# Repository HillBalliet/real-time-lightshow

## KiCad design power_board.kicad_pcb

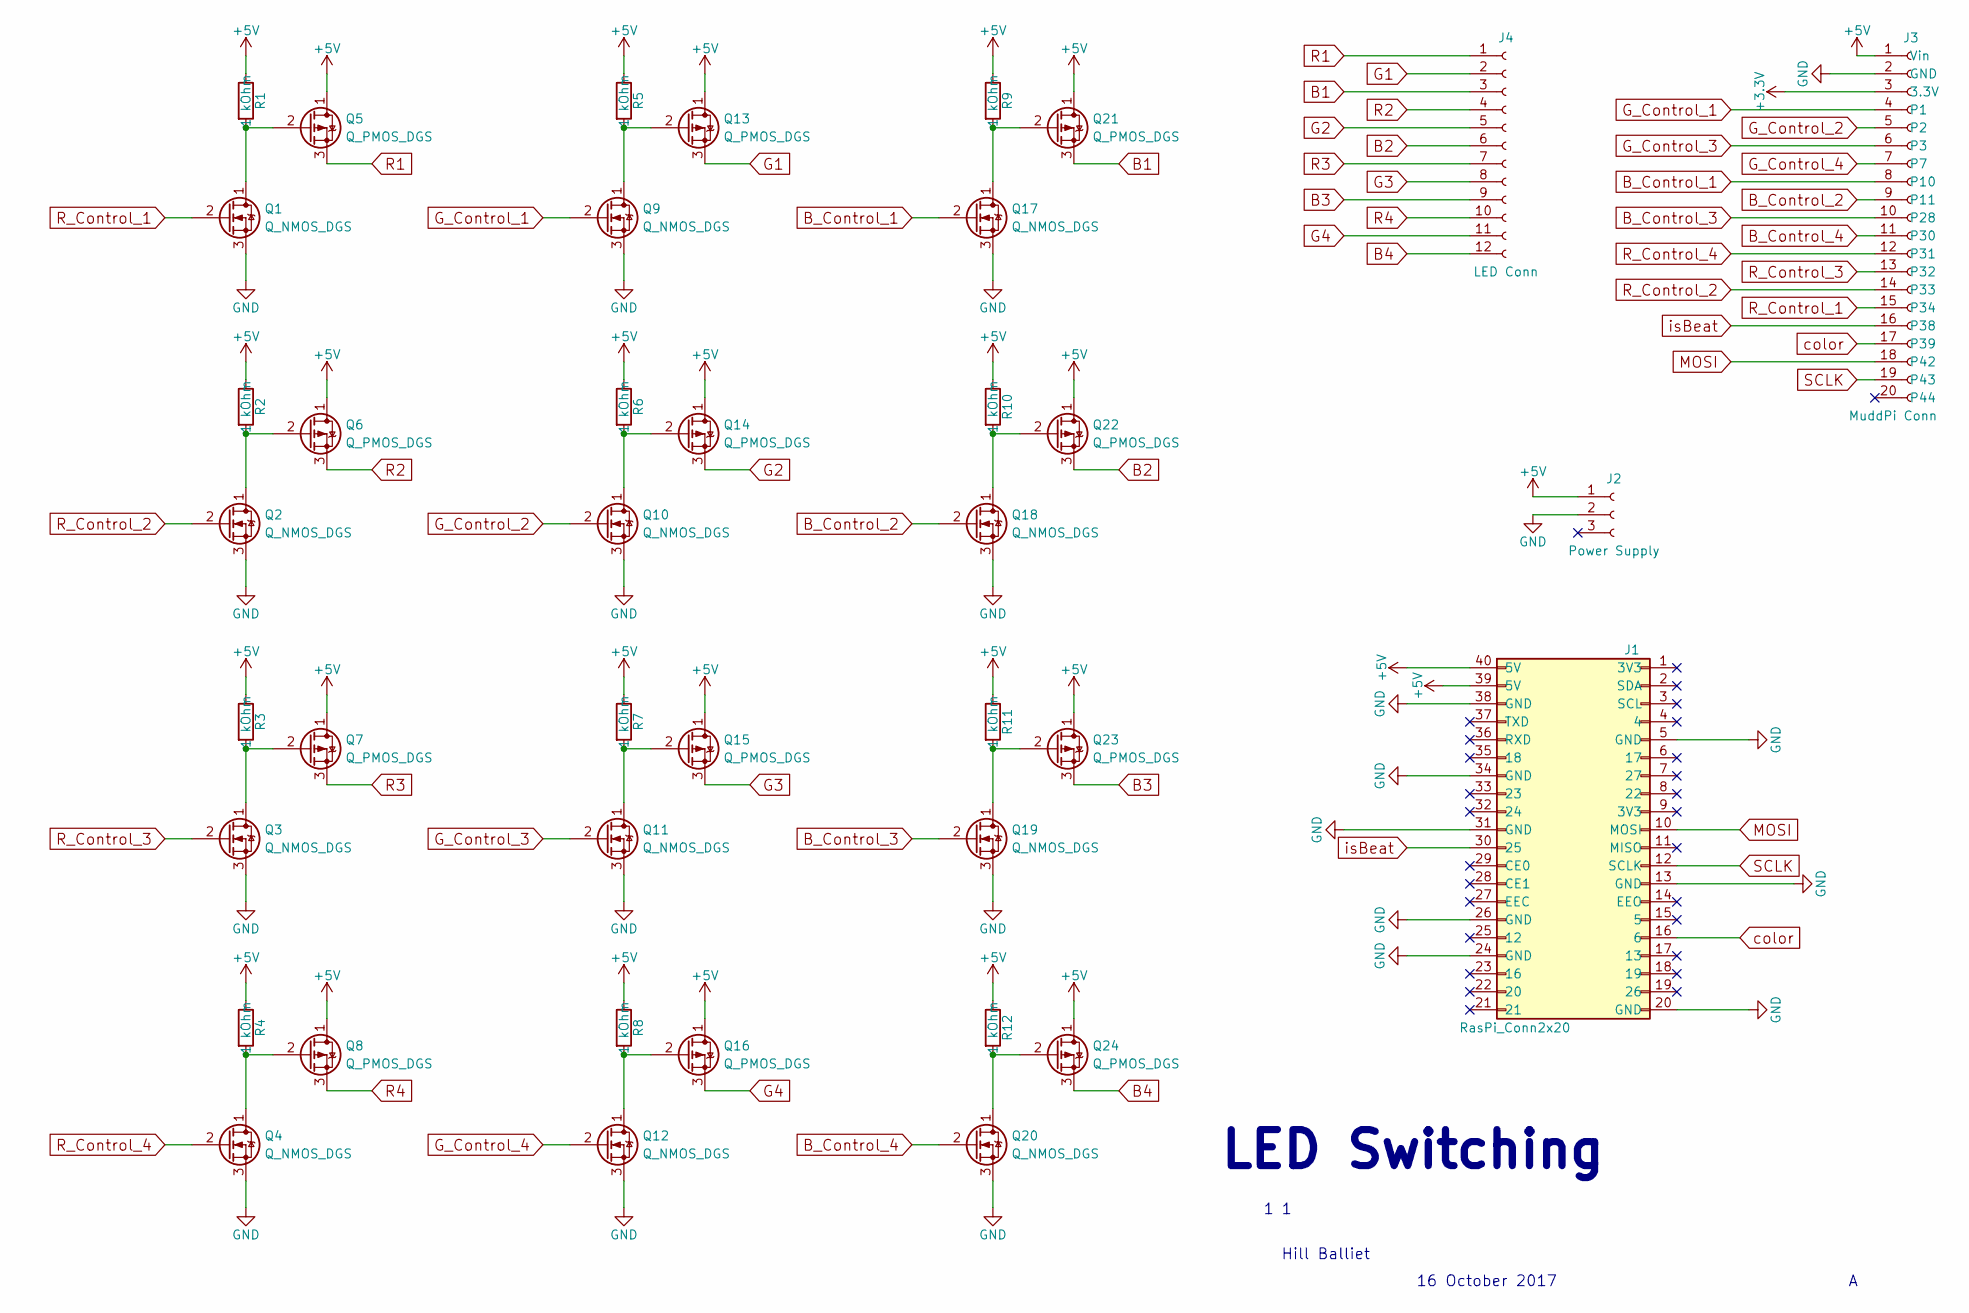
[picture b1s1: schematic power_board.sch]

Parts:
J1: RasPi_Conn2x20; Molex_2x20
J2: Power Supply; BARREL_JACK
J3: MuddPi Conn; Molex_1x20; Manufacturer PN PPPC201LFBN-RC
J4: LED Conn; Molex_KK-6410-12_12x2.54mm_Straight
Q1, Q2, Q3, Q4, Q9, Q10, Q11, Q12, Q17, Q18, Q19, Q20: Q_NMOS_DGS; SOT-323FL; Drive Voltage 0.9, 4.5V; Manufacturer PN RU1J002YNTCL
Q5, Q6, Q7, Q8, Q13, Q14, Q15, Q16, Q21, Q22, Q23, Q24: Q_PMOS_DGS; SOT-23; Drive Voltage 2.5, 4.5V; Manufacturer PN DMP2215L-7
R1, R2, R3, R4, R5, R6, R7, R8, R9, R10, R11, R12: 1 kOhm; R_0402; Manufacturer PN CRG0402J1K0

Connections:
+3V3: J3.3 (3.3V)
+5V: J1.39 (5V), J1.40 (5V), J2.1, J3.1 (Vin), Q5.1 (D), Q6.1 (D), Q7.1 (D), Q8.1 (D), Q13.1 (D), Q14.1 (D), Q15.1 (D), Q16.1 (D), Q21.1 (D), Q22.1 (D), Q23.1 (D), Q24.1 (D), R1.1, R2.1, R3.1, R4.1, R5.1, R6.1, R7.1, R8.1, R9.1, R10.1, R11.1, R12.1
B1: J4.3, Q21.3 (S)
B2: J4.6, Q22.3 (S)
B3: J4.9, Q23.3 (S)
B4: J4.12, Q24.3 (S)
B_Control_1: J3.8 (P10), Q17.2 (G)
B_Control_2: J3.9 (P11), Q18.2 (G)
B_Control_3: J3.10 (P28), Q19.2 (G)
B_Control_4: J3.11 (P30), Q20.2 (G)
G1: J4.2, Q13.3 (S)
G2: J4.5, Q14.3 (S)
G3: J4.8, Q15.3 (S)
G4: J4.11, Q16.3 (S)
GND: J1.5 (GND), J1.13 (GND), J1.20 (GND), J1.24 (GND), J1.26 (GND), J1.31 (GND), J1.34 (GND), J1.38 (GND), J2.2, J3.2 (GND), Q1.3 (S), Q2.3 (S), Q3.3 (S), Q4.3 (S), Q9.3 (S), Q10.3 (S), Q11.3 (S), Q12.3 (S), Q17.3 (S), Q18.3 (S), Q19.3 (S), Q20.3 (S)
G_Control_1: J3.4 (P1), Q9.2 (G)
G_Control_2: J3.5 (P2), Q10.2 (G)
G_Control_3: J3.6 (P3), Q11.2 (G)
G_Control_4: J3.7, Q12.2 (G)
MOSI: J1.10 (MOSI), J3.18 (P42)
unnamed: Q1.1 (D), Q5.2 (G), R1.2
unnamed: Q2.1 (D), Q6.2 (G), R2.2
unnamed: Q3.1 (D), Q7.2 (G), R3.2
unnamed: Q4.1 (D), Q8.2 (G), R4.2
unnamed: Q10.1 (D), Q14.2 (G), R6.2
unnamed: Q11.1 (D), Q15.2 (G), R7.2
unnamed: Q12.1 (D), Q16.2 (G), R8.2
unnamed: Q9.1 (D), Q13.2 (G), R5.2
unnamed: Q17.1 (D), Q21.2 (G), R9.2
unnamed: Q18.1 (D), Q22.2 (G), R10.2
unnamed: Q19.1 (D), Q23.2 (G), R11.2
unnamed: Q20.1 (D), Q24.2 (G), R12.2
R1: J4.1, Q5.3 (S)
R2: J4.4, Q6.3 (S)
R3: J4.7, Q7.3 (S)
R4: J4.10, Q8.3 (S)
R_Control_1: J3.15 (P34), Q1.2 (G)
R_Control_2: J3.14 (P33), Q2.2 (G)
R_Control_3: J3.13 (P32), Q3.2 (G)
R_Control_4: J3.12 (P31), Q4.2 (G)
SCLK: J1.12 (SCLK), J3.19 (P43)
color: J1.16 (6), J3.17 (P39)
isBeat: J1.30 (25), J3.16 (P38)

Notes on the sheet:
LED Switching
16 October 2017
Hill Balliet

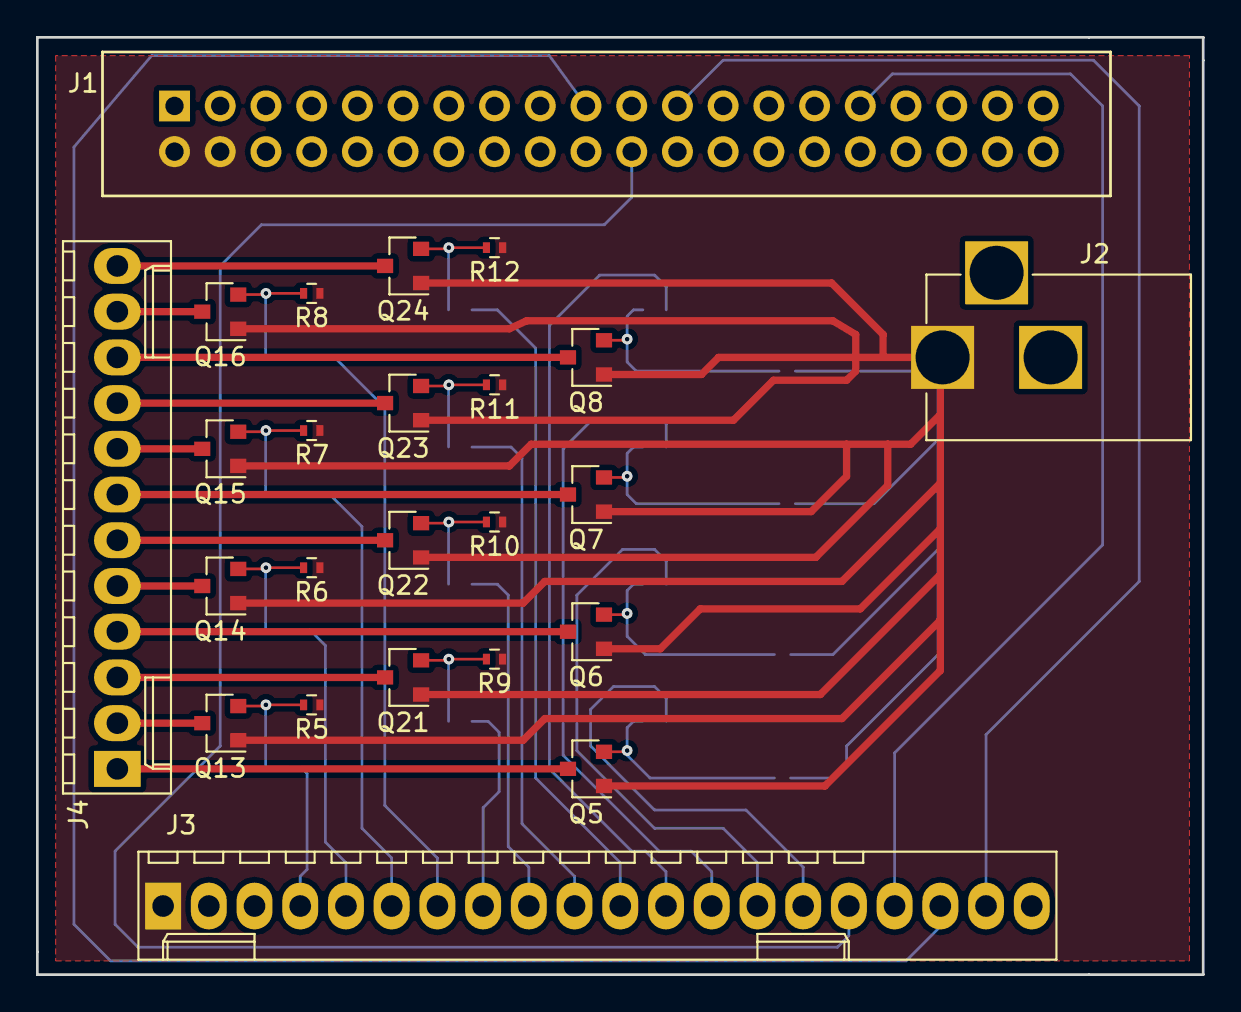
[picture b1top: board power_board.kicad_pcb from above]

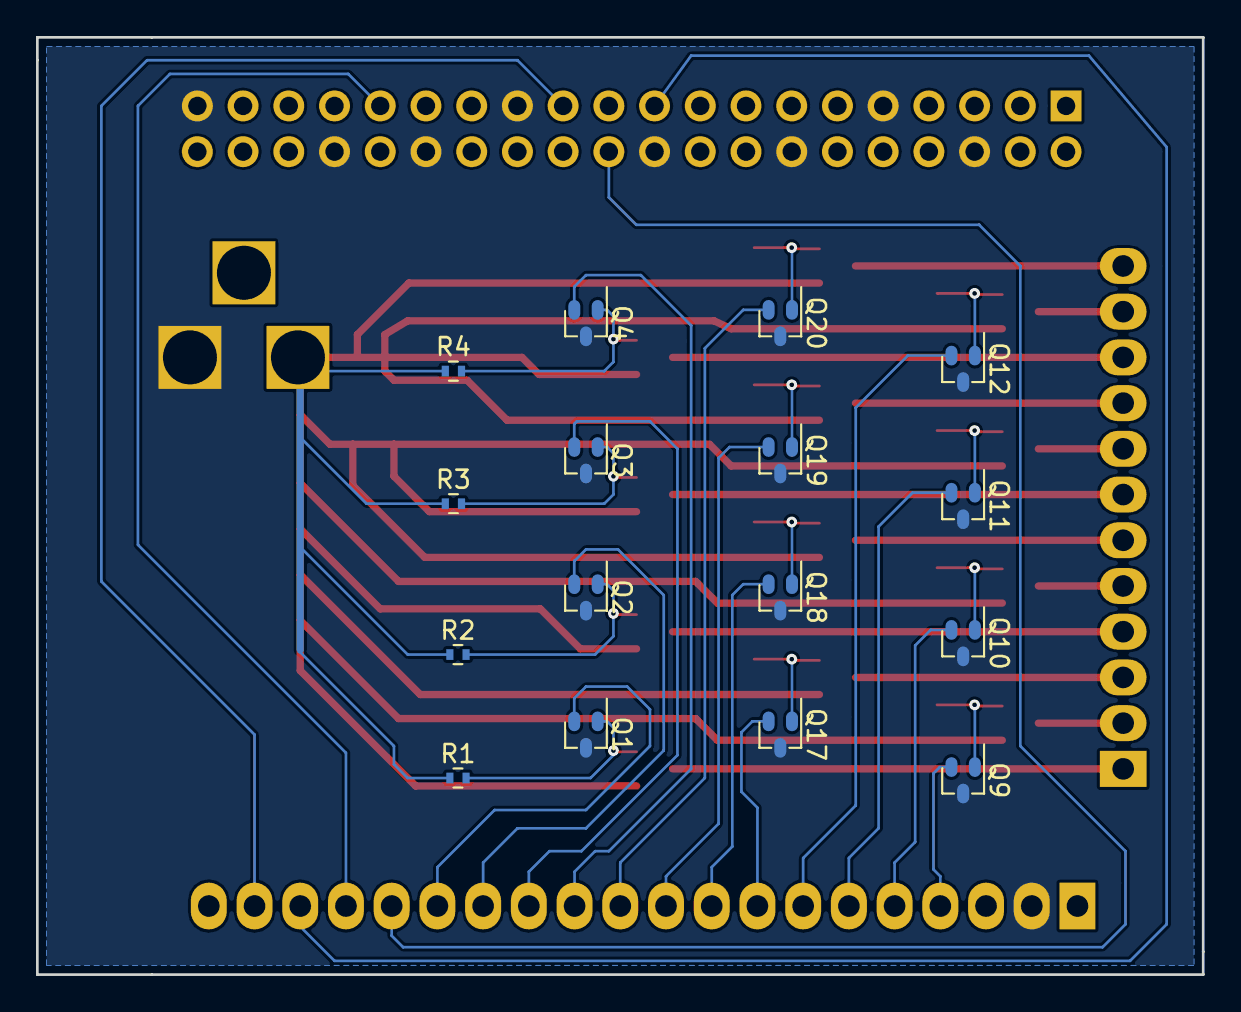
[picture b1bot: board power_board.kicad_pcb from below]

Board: 2 copper layers, 64.8 x 52.1 mm, 40 parts (16 on the bottom side), 42 nets.

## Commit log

2017-09-28 Adding code for the Rasberry Pi from the MicroPs final project.
2017-09-28 Adding more Raspberry Pi code for beat finding and audio data processing from the MicroPs final project. Also adding web controller documents for picking the color of the LEDs.
2017-09-28 Found the folder on Charlie with all of the final documents and loaded that into the Git Repo.
2017-09-28 List of potential parts. Currently includes 2 wall adapter alternatives
2017-10-02 Found mosfets for switching power to the LEDs
2017-10-03 removed the non-current/non-hardware files
2017-10-03 Found MOSFETs and started the KiCAD project
2017-10-05 Added to the list of parts and started putting parameters on parts in the schematic
2017-10-17 Finished schematics first draft for switching board and found all parts for the board
2017-10-18 Added footprint to the power supply jack. Fixed a wrong part (raspi connector was 10x2 is now 20x2)
2017-10-18 Improved schematic symbols and finished making all footprints. (Need to be checked before finalization)
2017-10-19 Added info for best board manufacturer and fixed issues with connections on the schematic. Checked pinouts
2017-10-19 Added schematic for the LED output connector
2017-10-22 Finished initial layout and changed the pinout of the MuddPi connector so that the board would be easier to route
2017-10-31 Fixed some issues with the layout and made it conform to the OSH Park manufacturing specifications. Ordered the board!!!
